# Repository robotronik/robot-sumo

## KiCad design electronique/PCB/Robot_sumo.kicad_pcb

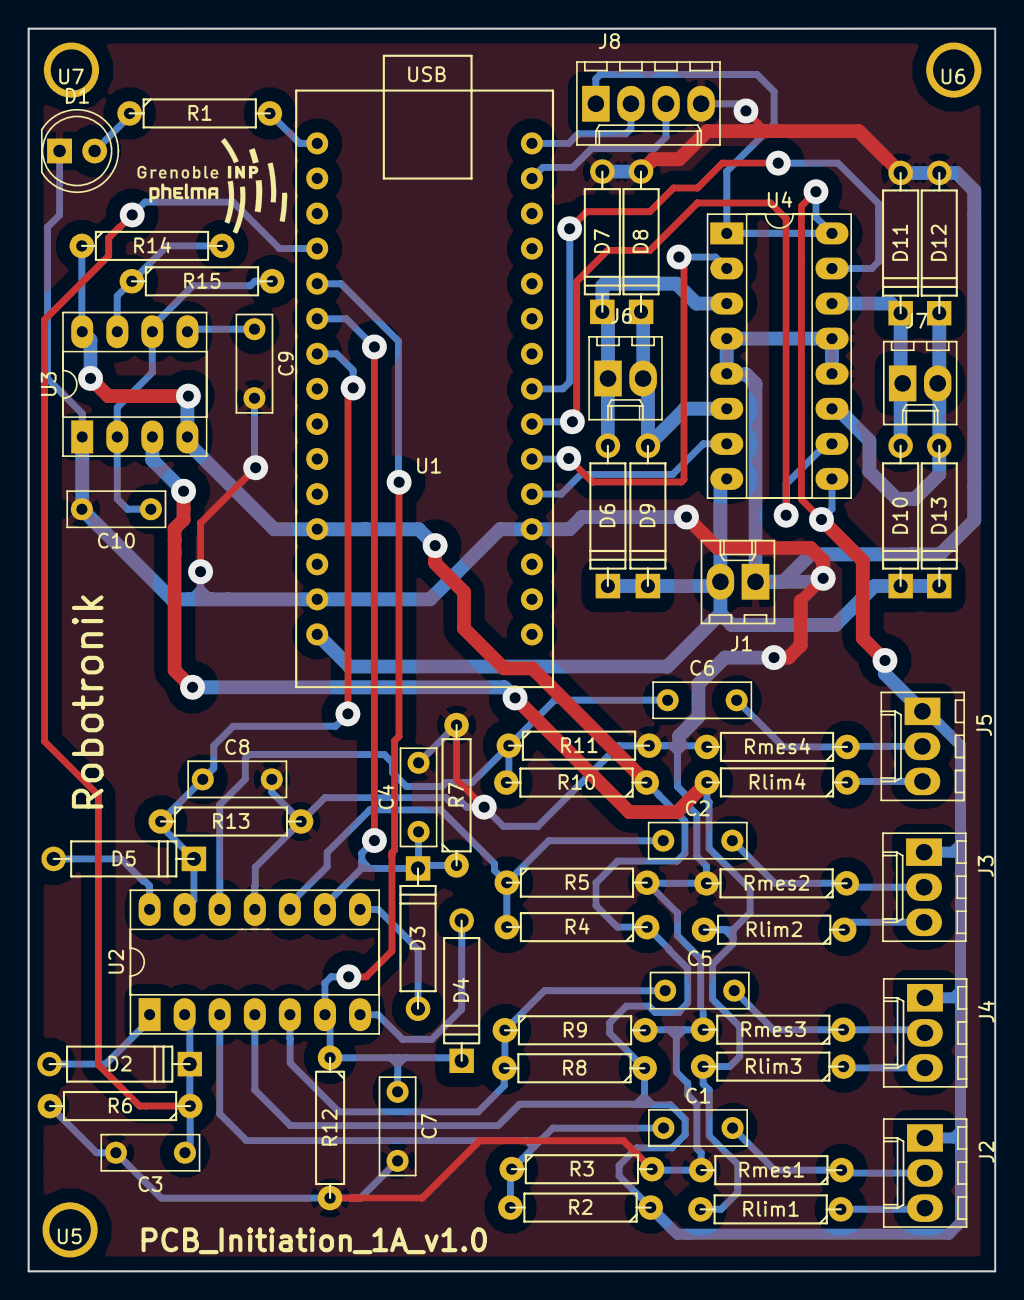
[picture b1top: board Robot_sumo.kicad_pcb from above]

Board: 2 copper layers, 70.0 x 90.0 mm, 61 parts (0 on the bottom side), 39 nets.

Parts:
C1, C2, C3, C4, C5, C6, C7, C8: C; C_Rect_L7.0mm_W2.5mm_P5.00mm
C9: 10nC; C_Rect_L7.0mm_W2.5mm_P5.00mm
C10: 4,8nC; C_Rect_L7.0mm_W2.5mm_P5.00mm
D1: LED; LED_D5.0mm
D2, D3, D4, D5: D; D4
D6, D7, D8, D9, D10, D11, D12, D13: D_ALT; D4
J1: CONN_Batt; Molex_KK-6410-02_02x2.54mm_Straight
J2: CONN_C1; Molex_KK-6410-03_03x2.54mm_Straight
J3: CONN_C3; Molex_KK-6410-03_03x2.54mm_Straight
J4: CONN_C2; Molex_KK-6410-03_03x2.54mm_Straight
J5: CONN_C4; Molex_KK-6410-03_03x2.54mm_Straight
J6: CONN_M1; Molex_KK-6410-02_02x2.54mm_Straight
J7: CONN_M2; Molex_KK-6410-02_02x2.54mm_Straight
J8: CONN_distance; Molex_KK-6410-04_04x2.54mm_Straight
R1, R2, R3, R4, R5, R6, R7, R8, R9, R10, R11, R12, R13: R; R4-LARGE_PADS
R14: 60kR; R4-LARGE_PADS
R15: 120kR; R4-LARGE_PADS
Rlim1, Rlim2, Rlim3, Rlim4: R; R4-LARGE_PADS
Rmes1, Rmes2, Rmes3, Rmes4: R; R4-LARGE_PADS
U1: Arduino-nano
U2: LM324; DIP-14_W7.62mm_Socket_LongPads
U3: NE555; DIP-8_W7.62mm_Socket_LongPads
U4: L293; DIP-16_W7.62mm_Socket_LongPads
U5, U6, U7: trou-3; Trou-3

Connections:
+5V: J2.1, J3.1, J4.1, J5.1, J8.1, R2.1, R4.1, R8.1, R10.1, R14.1, U1.12, U2.4, U3.4, U3.8, U4.1, U4.9, U4.16
/R-IR/C1: C3.1, D2.1, R6.1, U1.4, U2.2
/R-IR/C2: C7.1, D4.1, R12.1, U1.5, U2.6
/R-IR/C3: C4.1, D3.1, R7.1, U1.6, U2.9
/R-IR/C4: C8.1, D5.1, R13.1, U1.7, U2.13
/R-IR/Signal-e: Rlim1.2, Rlim2.2, Rlim3.2, Rlim4.2, U3.3
/distance_sensor/Echo: J8.3, U1.29
/distance_sensor/Trig: J8.2, U1.30
/motor-part/O1: U1.20, U4.7
/motor-part/O2: U1.22, U4.10
/motor-part/PWM1: U1.21, U4.2
/motor-part/PWM2: U1.23, U4.15
GND: C3.2, C4.2, C7.2, C8.2, C9.2, C10.2, D1.1, D7.2, D8.2, D11.2, D12.2, J1.1, J8.4, R3.2, R5.2, R6.2, R7.2, R9.2, R11.2, R12.2, R13.2, Rmes1.2, Rmes2.2, Rmes3.2, Rmes4.2, U1.14, U1.19, U2.11, U3.1, U4.4, U4.5, U4.12, U4.13
unnamed: C1.1, R2.2, R3.1, U2.3
unnamed: C1.2, J2.2, Rmes1.1
unnamed: C2.1, R4.2, R5.1, U2.10
unnamed: C2.2, J3.2, Rmes2.1
unnamed: C5.1, R8.2, R9.1, U2.5
unnamed: C5.2, J4.2, Rmes3.1
unnamed: C6.1, R10.2, R11.1, U2.12
unnamed: C6.2, J5.2, Rmes4.1
unnamed: C9.1, U3.5
unnamed: C10.1, R15.2, U3.2, U3.6
unnamed: D1.2, R1.1
unnamed: D2.2, U2.1
unnamed: D3.2, U2.8
unnamed: D4.2, U2.7
unnamed: D5.2, U2.14
unnamed: D6.2, D7.1, J6.1, U4.3
unnamed: D8.1, D9.2, J6.2, U4.6
unnamed: D10.2, D11.1, J7.1, U4.14
unnamed: D12.1, D13.2, J7.2, U4.11
unnamed: J2.3, Rlim1.1
unnamed: J3.3, Rlim2.1
unnamed: J4.3, Rlim3.1
unnamed: J5.3, Rlim4.1
unnamed: R1.2, U1.1
unnamed: R14.2, R15.1, U3.7
VCC: D6.1, D9.1, D10.1, D13.1, J1.2, U1.15, U4.8

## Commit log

2016-09-06 Modèle de la roue du moteur chinois
2016-09-06 Re-push
2016-09-06 3eme roue du robot
2016-09-06 Fichier Openscad de la carte Arduino Nano
2016-09-06 Fichier Openscad des pins pour la nano
2016-09-06 modelisation capteur ultrason
2016-09-07 modelasation amelioree + ajout couleurs
2016-09-08 Fichier Openscad de la breadboard
2016-09-08 Aperçu général en main
2016-09-08 Passage de nano, pinoche et breadboard en modules
2016-09-08 indentation + passage en modules
2016-09-13 modelisation base + robot + ajout capteur CNY70 + choix pour modules inclus dans main
2016-09-15 ajout performance fix
2016-09-15 ajout archive STL pour contourner blocage gitignore
2016-09-16 correction support moteur
2016-09-17 Correction support moteur + rectification modif base
2016-09-20 Plan de la base
2016-09-20 réorganisation du projet sumo
2016-09-21 modif dimension capteurUS + modif element robot sumo
2016-09-22 ajout support capteur infrarouge + piece anti-frottement roue/base + rendu complet robot
2016-10-24 modicfication taille + ajout encoche
2017-06-27 new US sensor support
2017-06-28 error correction + added a new US sensor support
2017-06-28 added some funny stuff on US sensor support + added new motor support
2017-07-01 added new color sensor support + some fix on US sensor and motor support
2017-07-09 added color sensor placement + beginning of pcb support
2017-07-10 added battery rack + end of PCB support
2017-07-11 added some <cable management> features
2017-07-23 beginning of model convertion from openscad to freecad
2017-07-25 end of base modelisation
2017-07-26 added color sensor support parts
2017-07-28 added motor fix freecad model + corrected screw hole position on scad model
2017-08-27 added stl file
2017-09-06 added pololu ball caster support openscad + stl file
2017-09-19 added new ball caster + support + some dimension change
2017-09-21 new values
2017-10-08 Programmation robot sumo
2017-10-09 Suppression de l293.pdf
2017-10-10 Commentaires + mode test
2017-10-19 debug
2018-09-17 essai de simplification pour les 1a
2018-09-27 les fonctions de test marchent correctement
